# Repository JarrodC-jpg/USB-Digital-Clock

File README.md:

# USB-Digital-Clock
Usb powered digital clock

Written by: Jarrod Coffin

Press top or bottom button to turn off center lights

To set the time:
1. Press and hold the top button until center lights start blinking
2. Top button adjust the hour, bottom button adjust minutes
3. Press and hold top button to set time, the center lights will stop blinking
4. To back out of time set without saveing press and hold the bottom button

*Note: The time currently gaines a few seconds a day resulting in about a 1 minute time loss over the course of a few days. Still need to squash that timing bug. If you have an idea of how to fix that, create a new branch and take a shot. If it fixes the issue we will merger it to the master.

If you would like a board and parts, contact me at harris.ee.projects@gmail.com

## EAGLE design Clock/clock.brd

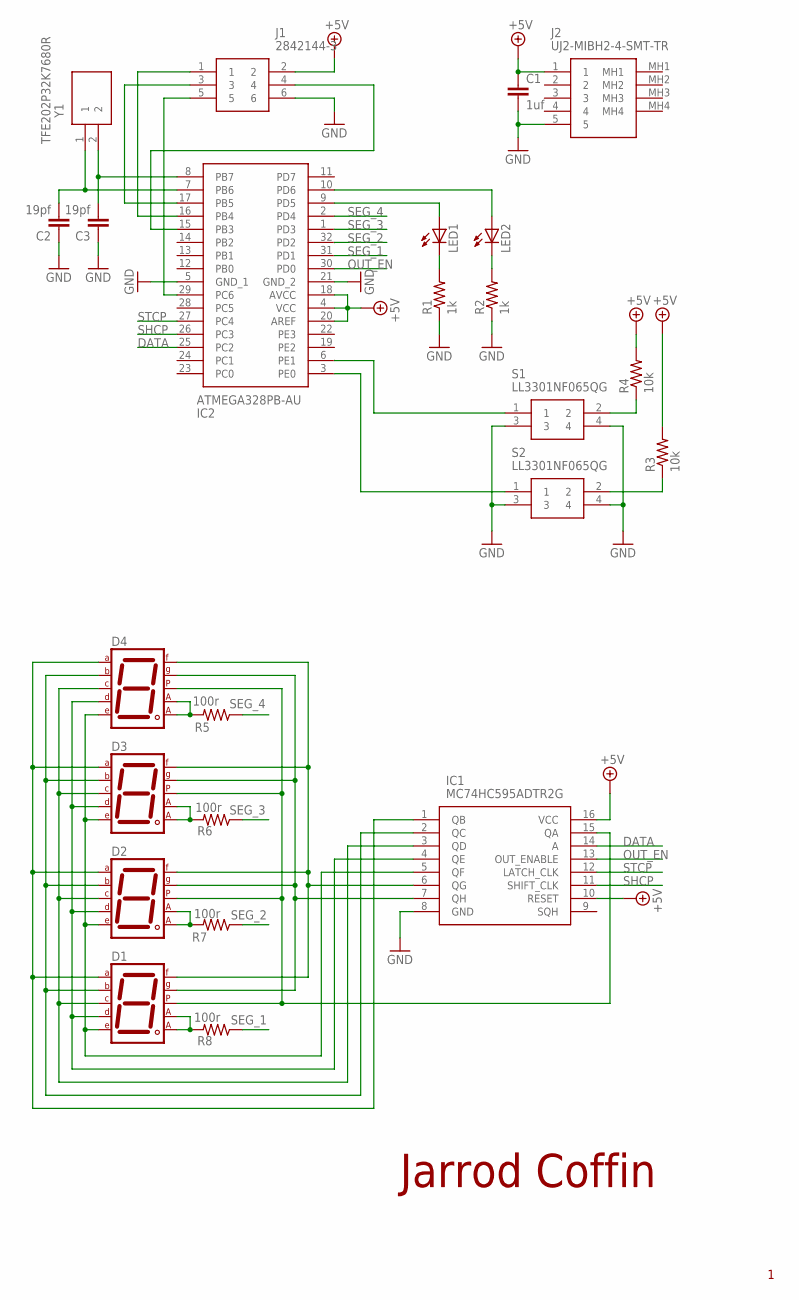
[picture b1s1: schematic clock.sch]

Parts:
C1: 1uf; C0805
C2, C3: 19pf; C0603
D1, D2, D3, D4: 7SEG-CA; 7SEG-13
IC1: MC74HC595ADTR2G; SOP65P640X120-16N
IC2: ATMEGA328PB-AU; QFP80P900X900X120-32N
J1: 2842144-3; HUSSP6W50P200_2X3_600X400X590P
J2: UJ2-MIBH2-4-SMT-TR; UJ2MIBH24SMTTR
LED1, LED2: LED3MM
R1, R2: 1k; R0805
R3, R4: 10k; R0805
R5, R6, R7, R8: 100r; R0805
S1, S2: LL3301NF065QG
Y1: TFE202P32K7680R

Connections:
+5V: C1.1, IC1.10 (RESET), IC1.16 (VCC), IC2.4 (VCC), IC2.18 (AVCC), IC2.20 (AREF), J1.2, J2.1, R3.2, R4.2
DATA: IC1.14 (A), IC2.25 (PC2)
GND: C1.2, C2.1, C3.1, IC1.8 (GND), IC2.5 (GND_1), IC2.21 (GND_2), J1.6, J2.5, R1.1, R2.1, S1.3, S1.4, S2.3, S2.4
unnamed: D1.10 (G), D2.10 (G), D3.10 (G), D4.10 (G), IC1.7 (QH)
unnamed: D1.9 (F), D2.9 (F), D3.9 (F), D4.9 (F), IC1.6 (QG)
unnamed: LED1.K (C), R1.2
unnamed: LED2.K (C), R2.2
unnamed: IC2.9 (PD5), LED1.A
unnamed: IC2.10 (PD6), LED2.A
unnamed: D1.5 (DP), D2.5 (DP), D3.5 (DP), D4.5 (DP), IC1.15 (QA)
unnamed: D1.1 (E), D2.1 (E), D3.1 (E), D4.1 (E), IC1.5 (QF)
unnamed: D1.2 (D), D2.2 (D), D3.2 (D), D4.2 (D), IC1.4 (QE)
unnamed: D1.4 (C), D2.4 (C), D3.4 (C), D4.4 (C), IC1.3 (QD)
unnamed: D1.6 (B), D2.6 (B), D3.6 (B), D4.6 (B), IC1.2 (QC)
unnamed: D1.7 (A), D2.7 (A), D3.7 (A), D4.7 (A), IC1.1 (QB)
unnamed: IC2.29 (PC6), J1.5
unnamed: IC2.15 (PB3), J1.4
unnamed: IC2.16 (PB4), J1.1
unnamed: IC2.17 (PB5), J1.3
unnamed: R4.1, S1.2
unnamed: R3.1, S2.2
unnamed: C2.2, IC2.7 (PB6), Y1.1
unnamed: IC2.3 (PE0), S2.1
unnamed: IC2.6 (PE1), S1.1
unnamed: D1.3 (CA1), D1.8 (CA2), R8.2
unnamed: C3.2, IC2.8 (PB7), Y1.2
unnamed: D2.3 (CA1), D2.8 (CA2), R7.2
unnamed: D3.3 (CA1), D3.8 (CA2), R6.2
unnamed: D4.3 (CA1), D4.8 (CA2), R5.2
OUT_EN: IC1.13 (OUT_ENABLE), IC2.30 (PD0)
SEG_1: IC2.31 (PD1), R8.1
SEG_2: IC2.32 (PD2), R7.1
SEG_3: IC2.1 (PD3), R6.1
SEG_4: IC2.2 (PD4), R5.1
SHCP: IC1.11 (SHIFT_CLK), IC2.26 (PC3)
STCP: IC1.12 (LATCH_CLK), IC2.27 (PC4)

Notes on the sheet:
Jarrod Coffin

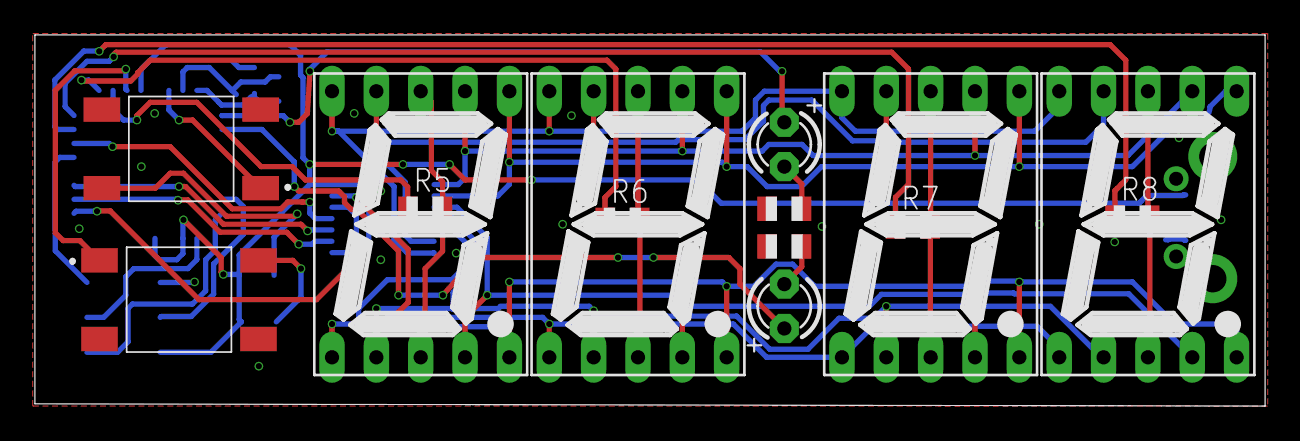
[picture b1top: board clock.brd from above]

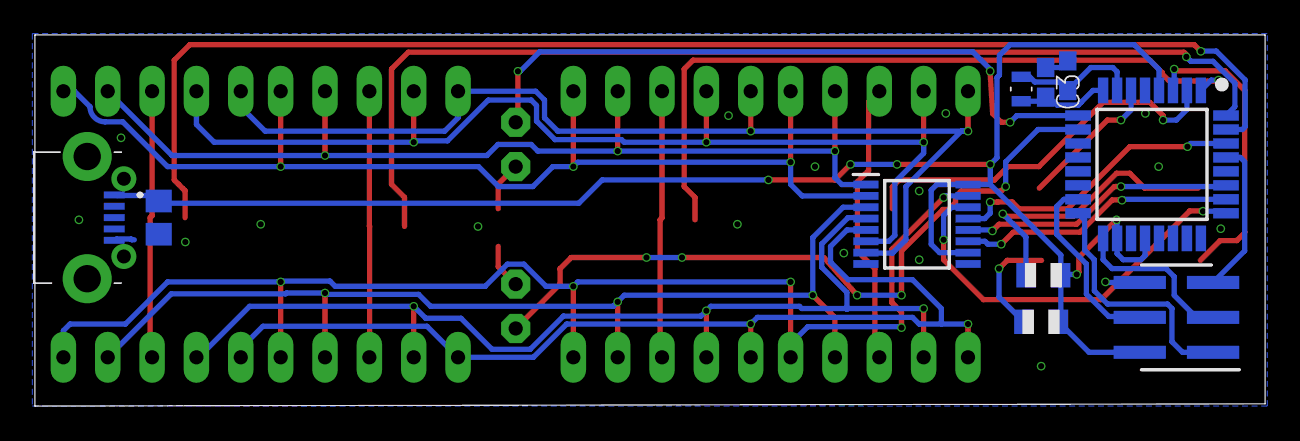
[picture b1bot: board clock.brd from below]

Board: 2 copper layers, 70.5 x 21.3 mm, 24 parts (10 on the bottom side), 36 nets.

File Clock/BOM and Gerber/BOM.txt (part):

Partlist exported from Y:/EE_Projects/Clock/Clock/clock.sch at 9/14/2020 6:51 PM

Qty Value              Device             Package                        Parts          Description                                                                                                                          ARROW_PART_NUMBER  ARROW_PRICE-STOCK                                                     DESCRIPTION                                                                                                                          HEIGHT MANUFACTURER_NAME MANUFACTURER_PART_NUMBER MOUSER_PART_NUMBER  MOUSER_PRICE-STOCK                                                                                               POPULARITY SPICEPREFIX
4                      7SEG-CA            7SEG-13                        D1, D2, D3, D4 7-segment DISPLAY                                                                                                                                                                                                                                                                                                                                                                                                                                                                                                                                                               
2                      C-EUC0603          C0603                          C2, C3         CAPACITOR, European symbol                                                                                                                                                                                                                                                                                                                                                                                                                                                                                                                                73         C          
2                      LED3MM             LED3MM                         LED1, LED2     LED                                                                                                                                                                                                                                                                                                                                                                                                                                                                                                                                                                             
4   100r               R-US_R0805         R0805                          R5, R6, R7, R8 RESISTOR, American symbol                                                                                                                                                                                                                                                                                                                                                                                                                                                                                                                                                       
2   10k                R-US_R0805         R0805                          R3, R4         RESISTOR, American symbol                                                                                                                                                                                                                                                                                                                                                                                                                                                                                                                                                       
2   1k                 R-US_R0805         R0805                          R1, R2         RESISTOR, American symbol                                                                                                                                                                                                                                                                                                                                                                                                                                                                                                                                                       
1   1uf                C-EUC0805          C0805                          C1             CAPACITOR, European symbol                                                                                                                                                                                                                                                                                                                                                                                                                                                                                                                                88         C          
1   2842144-3          2842144-3          HUSSP6W50P200_2X3_600X400X590P J1             Board to Board & Mezzanine Connectors 6P,2MM,BRK HDR,DRVT, SMD,0.76AU,TR W/CAP                                                       2842144-3                                                                                Board to Board & Mezzanine Connectors 6P,2MM,BRK HDR,DRVT, SMD,0.76AU,TR W/CAP                                                       mm     TE Connectivity   2842144-3                571-2842144-3       https://www.mouser.co.uk/ProductDetail/TE-Connectivity/28421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                                       
1   ATMEGA328PB-AU     ATMEGA328PB-AU     QFP80P900X900X120-32N          IC2            ATMEL - ATMEGA328PB-AU - MCU, 8BIT, ATMEGA, 20MHZ, TQFP-32                                                                           ATMEGA328PB-AU     https://www.arrow.com/en/products/atmega328pb-au/microchip-t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 ATMEL - ATMEGA328PB-AU - MCU, 8BIT, ATMEGA, 20MHZ, TQFP-32                                                                           1.2mm  Microchip         ATMEGA328PB-AU           556-ATMEGA328PB-AU  https://www.mouser.co.uk/ProductDetail/Microchip-Technology-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                       
2   LL3301NF065QG      LL3301NF065QG      LL3301NF065QG                  S1, S2         E-SWITCH - LL3301NF065QG - TACTILE SW, SPST, 0.05A, 12VDC, SOLDER                                                                    LL3301NF065QG                                                                            E-SWITCH - LL3301NF065QG - TACTILE SW, SPST, 0.05A, 12VDC, SOLDER                                                                    4mm    E-Switch          LL3301NF065QG            612-LL3301NF065QG   https://www.mouser.co.uk/ProductDetail/E-Switch/LL3301NF065Q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                                          
1   MC74HC595ADTR2G    MC74HC595ADTR2G    SOP65P640X120-16N              IC1            8-Bit Shift Register SER-SER/PAR TSSOP16 MC74HC595ADTR2G, 8-stage Shift Register, Serial to Serial/Parallel, 2  6 V, 16-Pin TSSOP-16                                                                                          8-Bit Shift Register SER-SER/PAR TSSOP16 MC74HC595ADTR2G, 8-stage Shift Register, Serial to Serial/Parallel, 2  6 V, 16-Pin TSSOP-16 1.2mm  ON Semiconductor  MC74HC595ADTR2G          863-MC74HC595ADTR2G https://www.mouser.com/Search/Refine.aspx?Keyword=863-MC74HC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
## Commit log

2020-10-09 Adding all files
2020-10-09 File management
2021-06-23 trying to fix shit
